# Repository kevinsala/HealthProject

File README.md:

# Health Project :pill:

This project aims to design and implement a portable HealthCare equipment. For the sensor interface, this project uses an **Arduino** Uno microcontroller. For connecting different sensors to the Arduino board, this project has also designed a **custom shield**. For controlling the interface, as well as showing the measurements results, this project uses an **Android application**.

:warning: **_Disclaimer: This Project is for educational and experimental purposes only. It should not be used for diagnostic or for medical operations of any sort._**:warning: 

## Available Measurements
* Electrocardiography and heart rate.
* Body temperature.
* Blood pressure.
* Oxygen saturation (SpO2).
* Respiratory rate.
* Lung capacity.

## Technical Features
* Android application to wirelessly control the hardware equipment.
* Bluetooth communication protocol between the hardware equipment and the application.
* ShiftBrite RGB LED control.
* Function LEDs control via _multiplexer_.
* Needs an external input voltatge (10V, -5V and GND input).

## Android Application
The next pictures shows the Android application and its friendly user interface. It has a page and instructions for each health functionality and a Bluetooth communication protocol, totally transparent to user. The application Project is located in the ['Android' folder](https://github.com/kevinsala/HealthProject/tree/master/Android).

_Menu of the Android application_

_Electrocardiography page of the Android application_

## Shield Design
The custom shield has been designed with [CadSoft EAGLE](http://www.cadsoftusa.com/) software. This design is completely functional and it has been tested. All related files are included in the ['Shield' folder](https://github.com/kevinsala/HealthProject/tree/master/Shield).

### Functional Block Diagram
The next figure represents the functional block diagram of the designed equipment.

_Functional block diagram_

### Electronic schematic

_Electronic schematic of the shield_
### Board Design

_Board design without conductive tracks_

_Board design with conductive tracks (Complete)_

## Arduino Software
The Arduino code is located in the ['Arduino' folder](https://github.com/kevinsala/HealthProject/tree/master/Arduino). It contains the implementation of all the features except the blood pressure measurement.

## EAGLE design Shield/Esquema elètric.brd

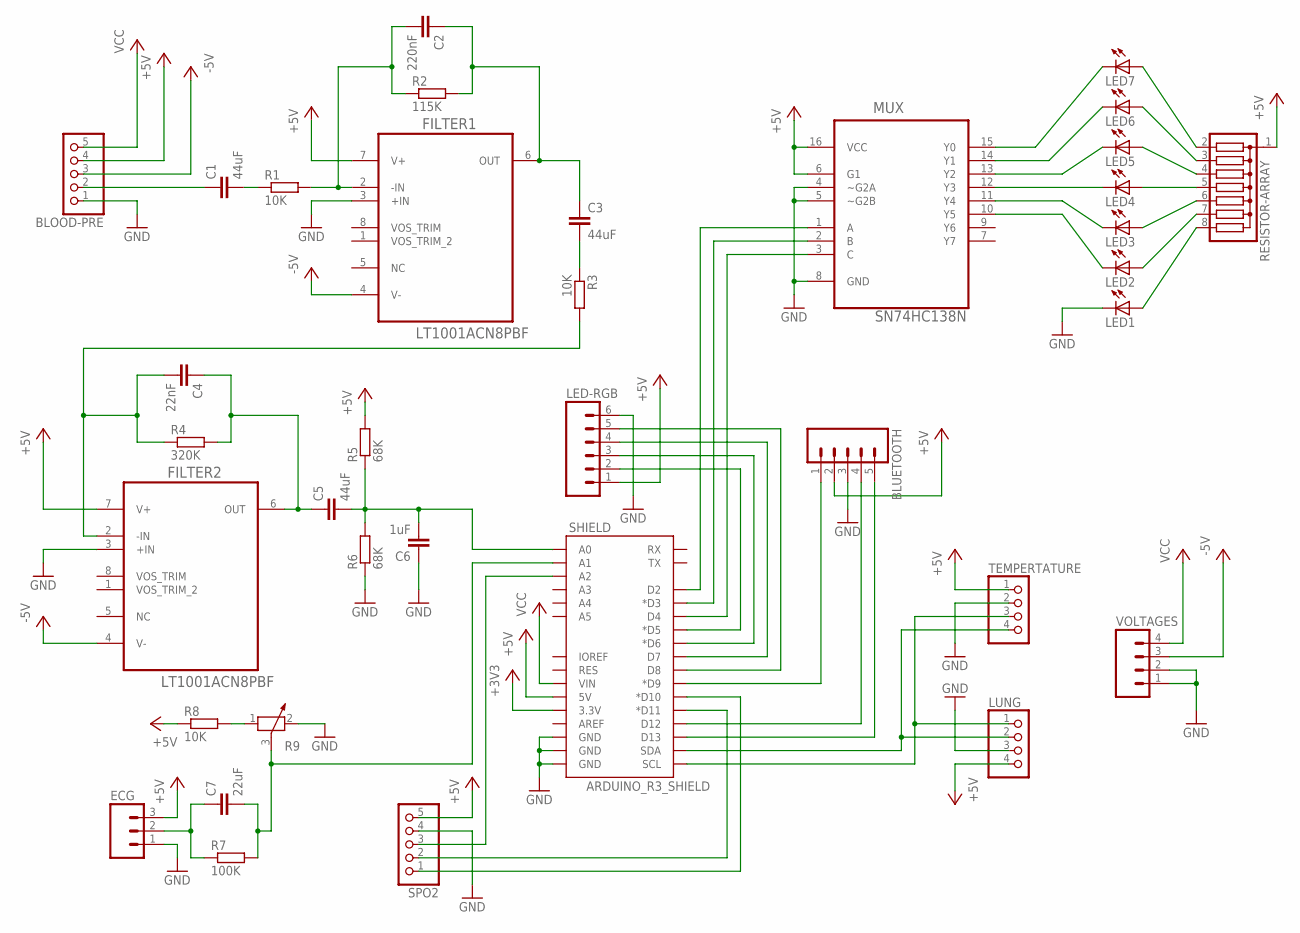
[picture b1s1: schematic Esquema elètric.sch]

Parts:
BLOOD-PRE: PINHD-1X5; 1X05
BLUETOOTH: M05PTH; 1X05
C1, C3, C5: 44uF; C050-050X075
C2: 220nF; C050-024X044
C4: 22nF; C050-024X044
C6: 1uF; C050-050X075
C7: 22uF; C050-050X075
ECG: M03PTH; 1X03
FILTER1, FILTER2: LT1001ACN8PBF; DIP254P762X393-8
LED1, LED2, LED3, LED4, LED5, LED6, LED7: LED5MM
LED-RGB: M06SILK_FEMALE_PTH; 1X06
LUNG: PINHD-1X4; 1X04
MUX: SN74HC138N; DIP254P762X508-16
R1, R3, R8: 10K; 0204/7
R2: 115K; 0204/7
R4: 320K; 0204/7
R5, R6: 68K; 0204/7
R7: 100K; 0204/7
R9: POTENTIOMETER_PT-10; PT-10
RESISTOR-ARRAY: G07R; SIL8
SHIELD: ARDUINO_R3_SHIELD; UNO_R3_SHIELD
SPO2: PINHD-1X5; 1X05
TEMPERTATURE: PINHD-1X4; 1X04
VOLTAGES: M04JST; 1X04-1.5MM_JST

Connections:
+3V3: SHIELD.3.3V
+5V: BLOOD-PRE.4, BLUETOOTH.2, ECG.3, FILTER1.7 (V+), FILTER2.7 (V+), LED-RGB.1, LUNG.4, MUX.6 (G1), MUX.16 (VCC), R5.2, R8.1, RESISTOR-ARRAY.1, SHIELD.5V, SPO2.5, TEMPERTATURE.1
-5V: BLOOD-PRE.3, FILTER1.4 (V-), FILTER2.4 (V-), VOLTAGES.3
GND: BLOOD-PRE.1, BLUETOOTH.3, C6.1, ECG.1, FILTER1.3 (+IN), FILTER2.3 (+IN), LED1.K (C), LED-RGB.6, LUNG.3, MUX.4 (~G2A), MUX.5 (~G2B), MUX.8 (GND), R6.1, R9.2, SHIELD.GND@0 (GND), SHIELD.GND@1 (GND), SHIELD.GND@2 (GND), SPO2.4, TEMPERTATURE.2, VOLTAGES.1, VOLTAGES.2
unnamed: LED7.K (C), MUX.15 (Y0)
unnamed: BLOOD-PRE.2, C1.1
unnamed: LED6.K (C), MUX.14 (Y1)
unnamed: LED-RGB.2, SHIELD.D5 (*D5)
unnamed: LED5.K (C), MUX.13 (Y2)
unnamed: LED3.K (C), MUX.11 (Y4)
unnamed: BLUETOOTH.4, SHIELD.D12
unnamed: LUNG.2, SHIELD.SDA, TEMPERTATURE.4
unnamed: MUX.1 (A), SHIELD.D2
unnamed: LED4.K (C), MUX.12 (Y3)
unnamed: LED2.K (C), MUX.10 (Y5)
unnamed: LED7.A, RESISTOR-ARRAY.2
unnamed: C7.1, ECG.2, R7.1
unnamed: LED6.A, RESISTOR-ARRAY.3
unnamed: BLUETOOTH.5, SHIELD.D13
unnamed: LED-RGB.5, SHIELD.D8
unnamed: LED5.A, RESISTOR-ARRAY.4
unnamed: LED4.A, RESISTOR-ARRAY.5
unnamed: C7.2, R7.2, R9.3, SHIELD.A1
unnamed: LED3.A, RESISTOR-ARRAY.6
unnamed: LED2.A, RESISTOR-ARRAY.7
unnamed: LED1.A, RESISTOR-ARRAY.8
unnamed: C4.1, C5.1, FILTER2.6 (OUT), R4.2
unnamed: BLUETOOTH.1, SHIELD.D9 (*D9)
unnamed: LED-RGB.4, SHIELD.D7
unnamed: R8.2, R9.1
unnamed: MUX.2 (B), SHIELD.D3 (*D3)
unnamed: MUX.3 (C), SHIELD.D4
unnamed: C4.2, FILTER2.2 (-IN), R3.2, R4.1
unnamed: C2.1, C3.1, FILTER1.6 (OUT), R2.2
unnamed: C3.2, R3.1
unnamed: C2.2, FILTER1.2 (-IN), R1.2, R2.1
unnamed: C1.2, R1.1
unnamed: C5.2, C6.2, R5.1, R6.2, SHIELD.A0
unnamed: LUNG.1, SHIELD.SCL, TEMPERTATURE.3
unnamed: SHIELD.A2, SPO2.3
unnamed: SHIELD.D11 (*D11), SPO2.2
unnamed: LED-RGB.3, SHIELD.D6 (*D6)
unnamed: SHIELD.D10 (*D10), SPO2.1
VCC: BLOOD-PRE.5, SHIELD.VIN, VOLTAGES.4

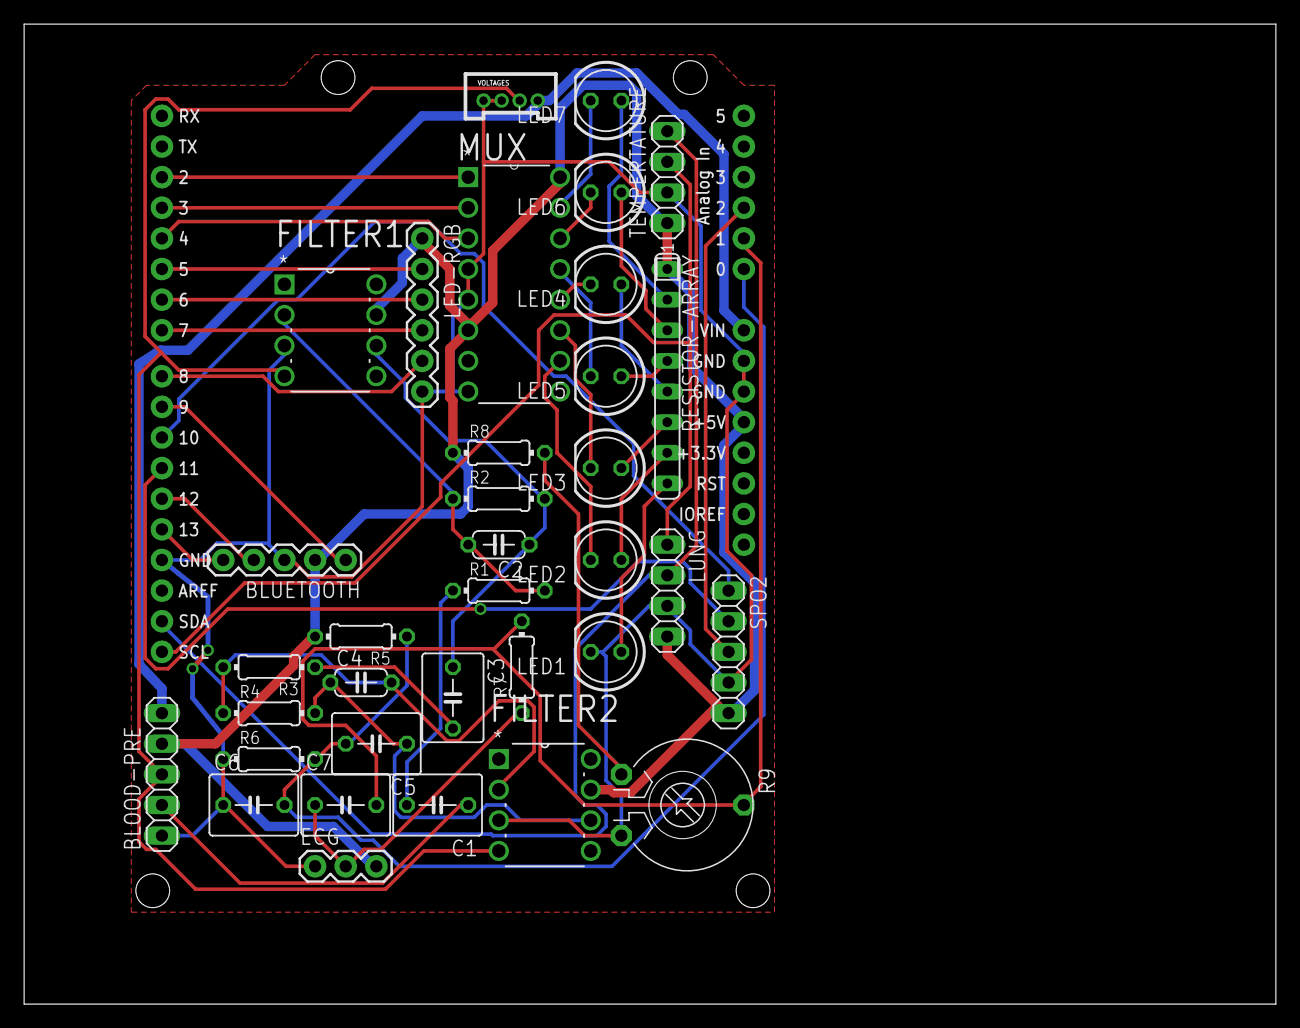
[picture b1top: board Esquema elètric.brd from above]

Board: 2 copper layers, 103.8 x 81.3 mm, 36 parts (0 on the bottom side), 43 nets.

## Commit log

2015-11-22 View Pager and basic fragments
2015-11-22 Icons
2015-11-22 PagerTitleStrip
2015-11-24 Animations
2015-11-24 Three generic screens
2015-12-02 Connection threads
2015-12-02 Structure and aChartEngine
2015-12-05 ECG design
2015-12-05 ECG Interface and charts completed
2015-12-06 Bluetooth protocol (to be tested)
2015-12-06 Bluetooth configuration updated (without discovery and not supported Bluetooth feature)
2015-12-18 :lollipop: Added .gitattributes
2015-12-18 Serial Communication & PSO2 measurement
    Added support for Serial Communication via Strings, specifying actions
    for each feature.
    Added support for measurement of the PSO2. By the way, the measurement
    process is not finished yet.
2015-12-22 RGB Led Library and Spo2 Library
    Defined Library Structure and implemented RGB Led Library and Spo2
    library
2015-12-22 Integrated custom library interface to main.ino
2015-12-22 Removed readme.txt
2016-01-02 Layouts updated
2016-01-11 Changed folder structure; Added most of the libraries
2016-01-15 Update of lung capacity
2016-01-16 Bluetooth library added
    Now we can receive and send messages via Bluetooth
2016-01-17 Bluetooth protocol and structure updated
2016-01-17 ECG class added and some changes to the main function
2016-01-19 Added Setup() function
2016-01-19 Added RespiratoryRate Library.
2016-01-19 RespiratoryRate completed
    In lacks adjusting RespIncrease (at RespiratoryRate.h). This is the
    value of the temp increase due to an exhalation.
2016-01-19 All functionalities implemented
2016-01-19 Spo2 finished
    Needs testing, but should be fine.
2016-01-19 Spo2 updated to double
    Needs verification - Real life testing
2016-01-20 Varies coses
2016-01-20 Updated RespiratoryRate
2016-01-20 Updated LungCapacity
    It should work fine now :+1:
2016-01-20 Formula update for LungCapacity calculus
    Approximation to 'average' air density [Sea Level & 20ºC]
2016-01-20 Added setup() to LungCapacity
2016-01-20 Updated LungCapacity
    It now measures 1 sample every 0.5 seconds
2016-01-20 Some changes
2016-01-20 Restart implemented
2016-01-20 RGB Led showing function
2016-01-20 SPO2 output adjusted
    Now SPO2 outputs values between 95 and 100.
    It outputs 0 if something "strange" has happened (for example, no
    finger).
2016-01-20 SPO2 output adjusted
2016-01-20 LungCapacity updated
2016-01-20 Respiratory Rate updated
2016-01-20 Falta fer els de temperatura
2016-01-21 Units updated
2016-01-21 Respiratory Rate done
2016-01-28 Final commit of the Arduino project
2016-01-28 Final commit of the Android project
2016-01-28 Merged Android app with Arduino interface
2016-01-28 Revert "Final commit of the Android project"
    This reverts commit bac02e191afa0ae2ff20fd200417274fdeda7d19.
2016-01-28 Revert "Merged Android app with Arduino interface"
    This reverts commit 693d85f7053afbd59a8e8b7c1e48119f5641e258.
2016-01-28 Moving Android app to folder
2016-01-29 Custom shield added
2016-01-29 Pictures added to the Readme

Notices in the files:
parts and their libraries:
SparkFun-Boards: Licensing: Creative Commons ShareAlike 4.0 International - https://creativecommons.org/licenses/by-sa/4.0
